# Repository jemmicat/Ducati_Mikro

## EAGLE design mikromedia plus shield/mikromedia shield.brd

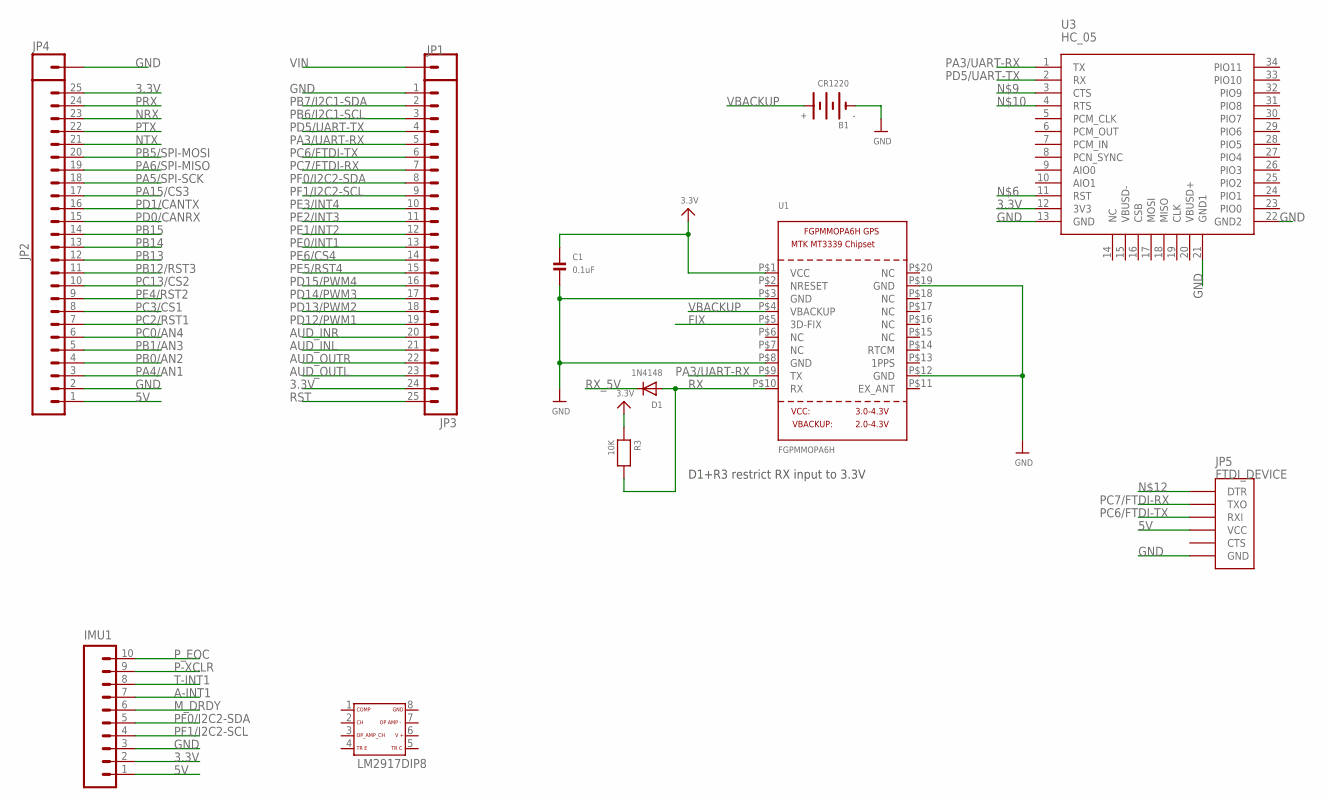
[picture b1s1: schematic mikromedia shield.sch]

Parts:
B1: CR1220
C1: 0.1uF; 0805
D1: 1N4148; SOD-323F
IC1: LM2917DIP8; LM2917_DIP8
IMU1: IMU; 1X10_LOCK_LONGPADS
JP1, JP4: M01PTH; 1X01
JP2, JP3: M25LOCK_LONGPADS; 1X25_LOCK_LONGPADS
JP5: FTDI_DEVICE; FTDI_DEVICE_SIDE
R3: 10K; 0805
U1: FGPMMOPA6H
U3: HC_05; BLUETOOTH_SMD

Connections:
3.3V: C1.1, IMU1.2, JP2.25, JP3.24, R3.1, U1.P$1 (VCC), U3.12 (3V3)
5V: IMU1.1, JP2.1, JP5.P$4 (VCC)
A-INT1: IMU1.7
AUD_INL: JP3.21
AUD_INR: JP3.20
AUD_OUTL: JP3.23
AUD_OUTR: JP3.22
FIX: U1.P$5 (3D-FIX)
GND: B1.-, C1.2, IMU1.3, JP2.2, JP3.1, JP4.1, JP5.P$6 (GND), U1.P$3 (GND), U1.P$8 (GND), U1.P$12 (GND), U1.P$19 (GND), U3.13 (GND), U3.21 (GND1), U3.22 (GND2)
M_DRDY: IMU1.6
NRX: JP2.23
NTX: JP2.21
P-XCLR: IMU1.9
PA3/UART-RX: JP3.5, U1.P$9 (TX), U3.1 (TX)
PA4/AN1: JP2.3
PA5/SPI-SCK: JP2.18
PA6/SPI-MISO: JP2.19
PA15/CS3: JP2.17
PB0/AN2: JP2.4
PB1/AN3: JP2.5
PB5/SPI-MOSI: JP2.20
PB6/I2C1-SCL: JP3.3
PB7/I2C1-SDA: JP3.2
PB12/RST3: JP2.11
PB13: JP2.12
PB14: JP2.13
PB15: JP2.14
PC0/AN4: JP2.6
PC2/RST1: JP2.7
PC3/CS1: JP2.8
PC6/FTDI-TX: JP3.6, JP5.P$3 (RXI)
PC7/FTDI-RX: JP3.7, JP5.P$2 (TXO)
PC13/CS2: JP2.10
PD0/CANRX: JP2.15
PD1/CANTX: JP2.16
PD5/UART-TX: JP3.4, U3.2 (RX)
PD12/PWM1: JP3.19
PD13/PWM2: JP3.18
PD14/PWM3: JP3.17
PD15/PWM4: JP3.16
PE0/INT1: JP3.13
PE1/INT2: JP3.12
PE2/INT3: JP3.11
PE3/INT4: JP3.10
PE4/RST2: JP2.9
PE5/RST4: JP3.15
PE6/CS4: JP3.14
PF0/I2C2-SDA: IMU1.5, JP3.8
PF1/I2C2-SCL: IMU1.4, JP3.9
PRX: JP2.24
PTX: JP2.22
P_EOC: IMU1.10
RST: JP3.25
RX: D1.A, R3.2, U1.P$10 (RX)
RX_5V: D1.C
T-INT1: IMU1.8
VBACKUP: B1.+$1 (+), U1.P$4 (VBACKUP)
VIN: JP1.1

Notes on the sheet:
D1+R3 restrict RX input to 3.3V

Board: 2 copper layers, 13 parts (0 on the bottom side), 11 nets, no tracks yet.

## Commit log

2014-01-01 Created
2014-01-01 Added Files
2014-07-23 added tinyGPS code
2014-07-27 added pc board
2014-07-29 Updated Screens
2014-07-29 added gps example
2014-07-29 removed unnecesary examples
2014-08-01 updated files
2014-08-01 added bmp085
2014-08-01 update pressure
2014-08-04 added examples
2014-08-04 gyro info
2014-08-05 redoing accelerometer stuff
2014-08-09 worked on screen data
2015-03-17 updated for imu
2015-03-17 fixed stuff
2015-03-18 added MPU Stuff
2015-03-19 more IMU stuff
2015-03-20 Added Case Model
2015-03-20 updated case models
2015-03-21 fixed holes
2015-03-24 On off switch location fixed
2015-03-24 added datasheets and GPS init code
2015-03-24 more gps info

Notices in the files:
parts and their libraries:
SparkFun-Connectors: Licensing: CC v3.0 Share-Alike You are welcome to use this library for commercial purposes.
